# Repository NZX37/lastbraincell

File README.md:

# LastBraincell

An e-paper device with joystick and buttons to write down reminders, a to-do list and basic references(like resistor table) as well as a calendar!

## CAD
Everything fits together with 3 M3 screws and heat set inserts.

The lid features holes for the joystick and microsd card.
It has two pieces.

## PCB

Simple two layer PCB.

Render from jlcpcb

3d viewer

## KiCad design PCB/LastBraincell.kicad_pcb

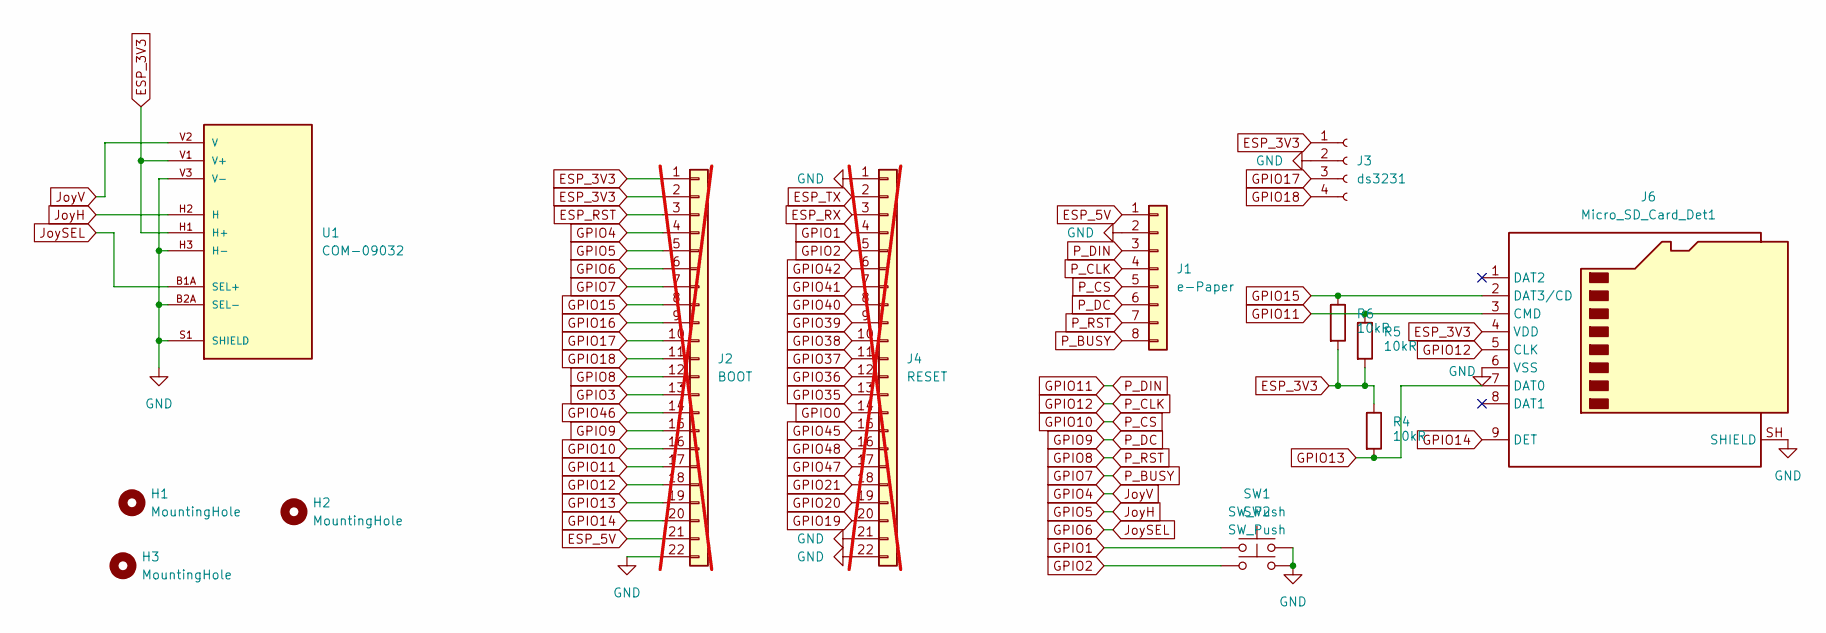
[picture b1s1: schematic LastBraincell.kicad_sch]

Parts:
H1, H2, H3: MountingHole; MountingHole_3.5mm
J1: e-Paper; PinSocket_1x08_P2.54mm_Vertical
J2: BOOT; PinSocket_1x22_P2.54mm_Vertical; not fitted
J3: ds3231; PinSocket_1x04_P2.54mm_Vertical
J4: RESET; PinSocket_1x22_P2.54mm_Vertical; not fitted
J6: Micro_SD_Card_Det1; microSD_HC_Molex_104031-0811
R4, R5, R6: 10kR; R_Axial_DIN0207_L6.3mm_D2.5mm_P10.16mm_Horizontal
SW1, SW2: SW_Push; SW_PUSH_6mm
U1: COM-09032; XDCR_COM-09032; PARTREV N/A

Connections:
ESP_3V3: J2.1, J2.2, J3.1, J6.4 (VDD), R4.1, R5.2, R6.2, U1.H1 (H+), U1.V1 (V+)
ESP_5V: J1.1, J2.21
ESP_RST: J2.3
ESP_RX: J4.3
ESP_TX: J4.2
GND: J1.2, J2.22, J3.2, J4.1, J4.21, J4.22, J6.6 (VSS), J6.SH (SHIELD), SW1.2, SW2.2, U1.B2A (SEL-), U1.H3 (H-), U1.S1 (SHIELD), U1.S2 (SHIELD), U1.S3 (SHIELD), U1.S4 (SHIELD), U1.V3 (V-)
GPIO0: J4.14
GPIO1: J4.4, SW1.1
GPIO2: J4.5, SW2.1
GPIO3: J2.13
GPIO4: J2.4, U1.V2 (V)
GPIO5: J2.5, U1.H2 (H)
GPIO6: J2.6, U1.B1A (SEL+)
GPIO7: J1.8, J2.7
GPIO8: J1.7, J2.12
GPIO9: J1.6, J2.15
GPIO10: J1.5, J2.16
GPIO11: J1.3, J2.17, J6.3 (CMD), R5.1
GPIO12: J1.4, J2.18, J6.5 (CLK)
GPIO13: J2.19, J6.7 (DAT0), R4.2
GPIO14: J2.20, J6.9 (DET)
GPIO15: J2.8, J6.2 (DAT3/CD), R6.1
GPIO16: J2.9
GPIO17: J2.10, J3.3
GPIO18: J2.11, J3.4
GPIO19: J4.20
GPIO20: J4.19
GPIO21: J4.18
GPIO35: J4.13
GPIO36: J4.12
GPIO37: J4.11
GPIO38: J4.10
GPIO39: J4.9
GPIO40: J4.8
GPIO41: J4.7
GPIO42: J4.6
GPIO45: J4.15
GPIO46: J2.14
GPIO47: J4.17
GPIO48: J4.16

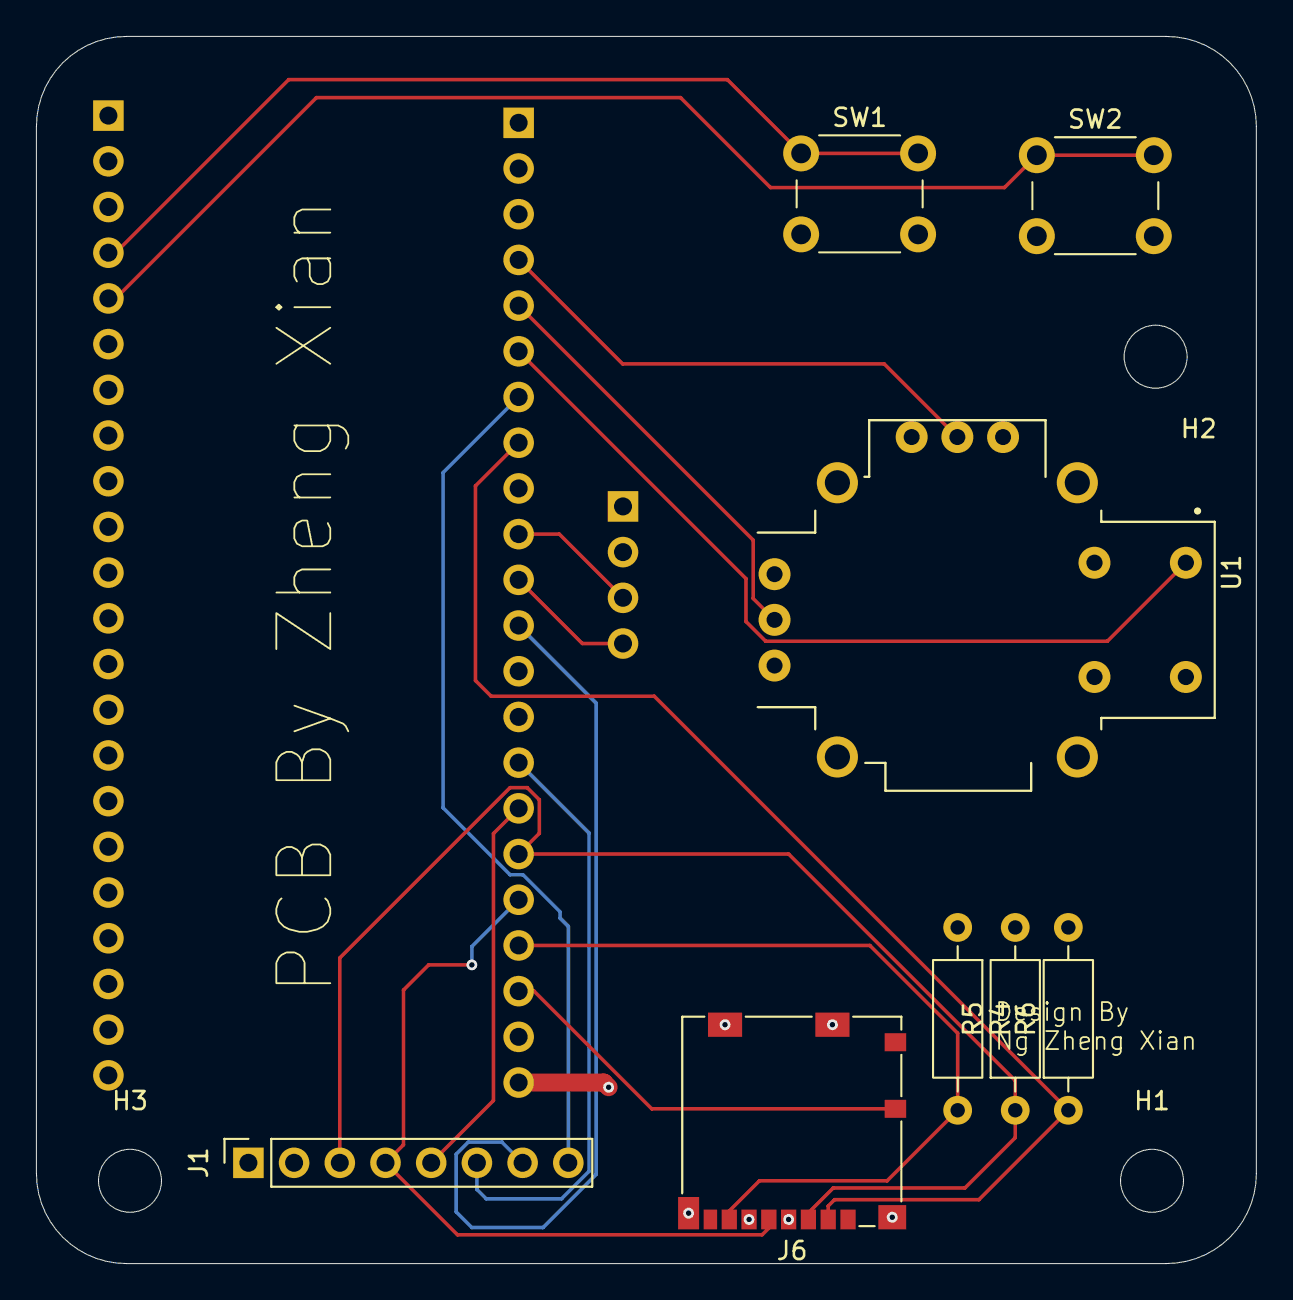
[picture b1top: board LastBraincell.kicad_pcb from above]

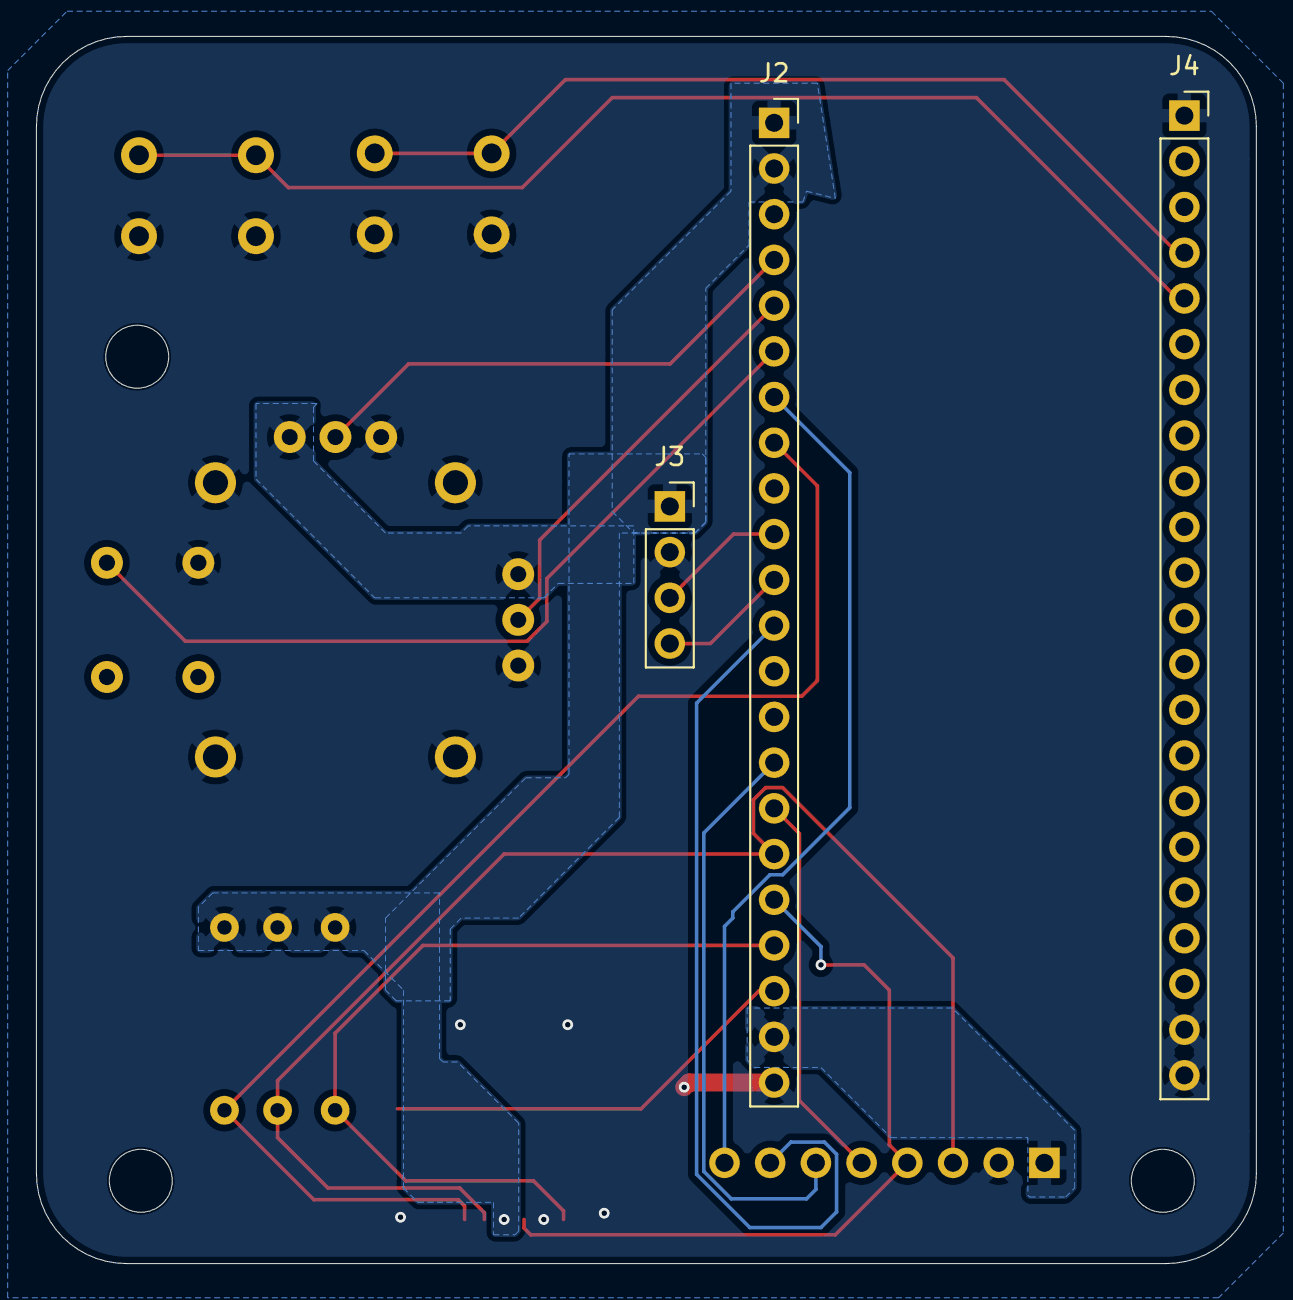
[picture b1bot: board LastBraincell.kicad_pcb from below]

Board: 2 copper layers, 67.8 x 68.2 mm, 14 parts (3 on the bottom side), 19 nets.
